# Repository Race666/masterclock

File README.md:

# Mutteruhrsteuerung

Firmware und Schaltungen zum Steuern von sog. Nebenuhren (z.B. Bahnhofsuhren)

Dokumentation und Details auf [albert-hetzles.de](http://albert-hetzles.de/mutteruhr/index.shtml)

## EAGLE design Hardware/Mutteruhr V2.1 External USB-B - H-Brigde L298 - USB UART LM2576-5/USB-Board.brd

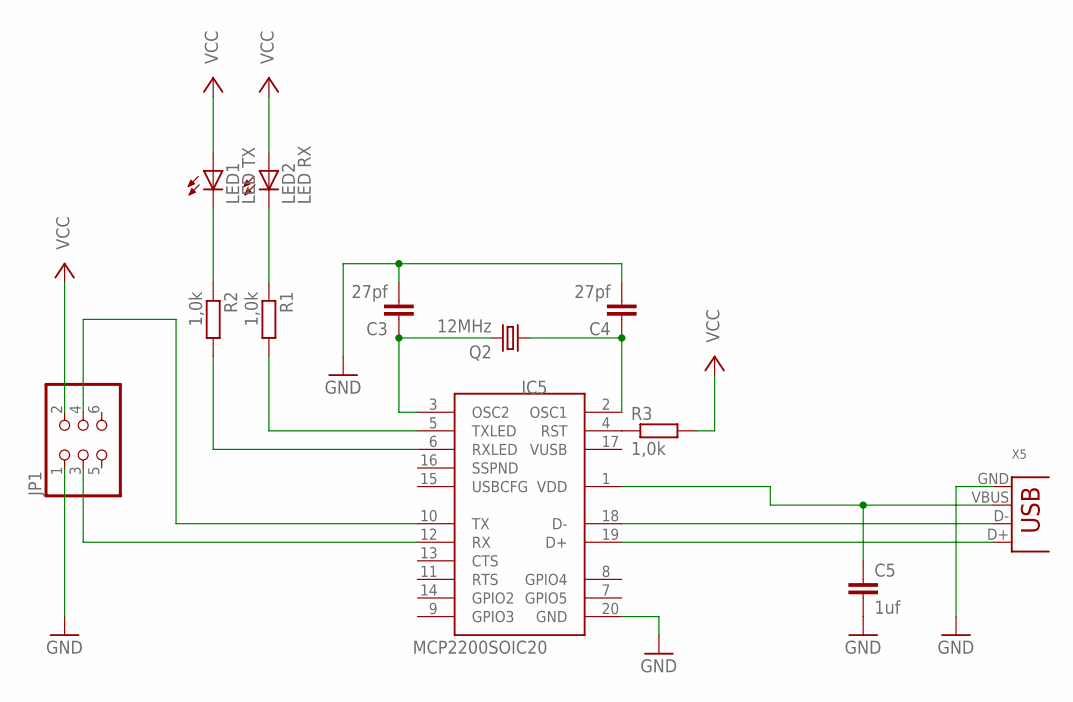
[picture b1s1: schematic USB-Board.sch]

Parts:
C3, C4: 27pf; C050-024X044
C5: 1uf; C5B5.5
IC5: MCP2200SOIC20; SOIC20
JP1: PINHD-2X3; 2X03
LED1: LED TX; LED3MM
LED2: LED RX; LED3MM
Q2: 12MHz; HC18U-V
R1, R2, R3: 1,0k; 0207/10
X5: USB-B-H

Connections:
GND: C3.2, C4.2, C5.2, IC5.20 (GND), JP1.1, X5.GND
unnamed: LED1.K (C), R2.1
unnamed: LED2.K (C), R1.1
unnamed: IC5.18 (D-), X5.D-
unnamed: IC5.19 (D+), X5.D+
unnamed: IC5.10 (TX), JP1.4
unnamed: IC5.12 (RX), JP1.3
unnamed: IC5.4 (RST), R3.1
unnamed: C3.1, IC5.3 (OSC2), Q2.2
unnamed: C4.1, IC5.2 (OSC1), Q2.1
unnamed: IC5.6 (RXLED), R2.2
unnamed: IC5.5 (TXLED), R1.2
unnamed: C5.1, IC5.1 (VDD), X5.VBUS
VCC: JP1.2, LED1.A, LED2.A, R3.2

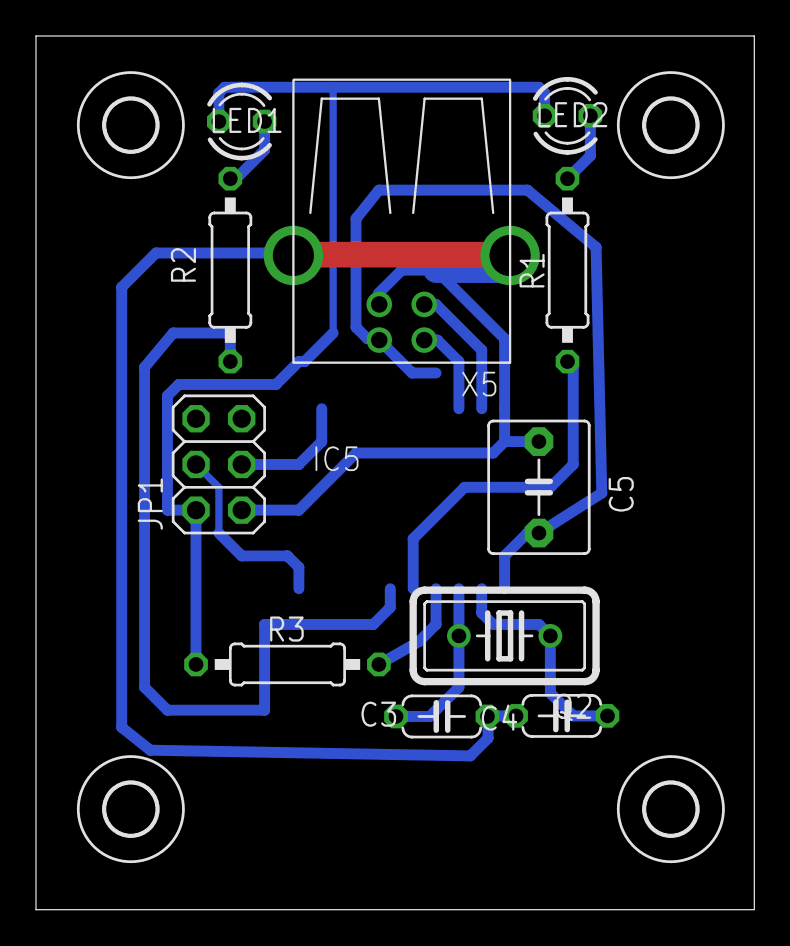
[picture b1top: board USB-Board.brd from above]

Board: 2 copper layers, 39.9 x 48.5 mm, 16 parts (1 on the bottom side), 14 nets.

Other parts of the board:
U$1, U$2, U$3, U$4: 2,8

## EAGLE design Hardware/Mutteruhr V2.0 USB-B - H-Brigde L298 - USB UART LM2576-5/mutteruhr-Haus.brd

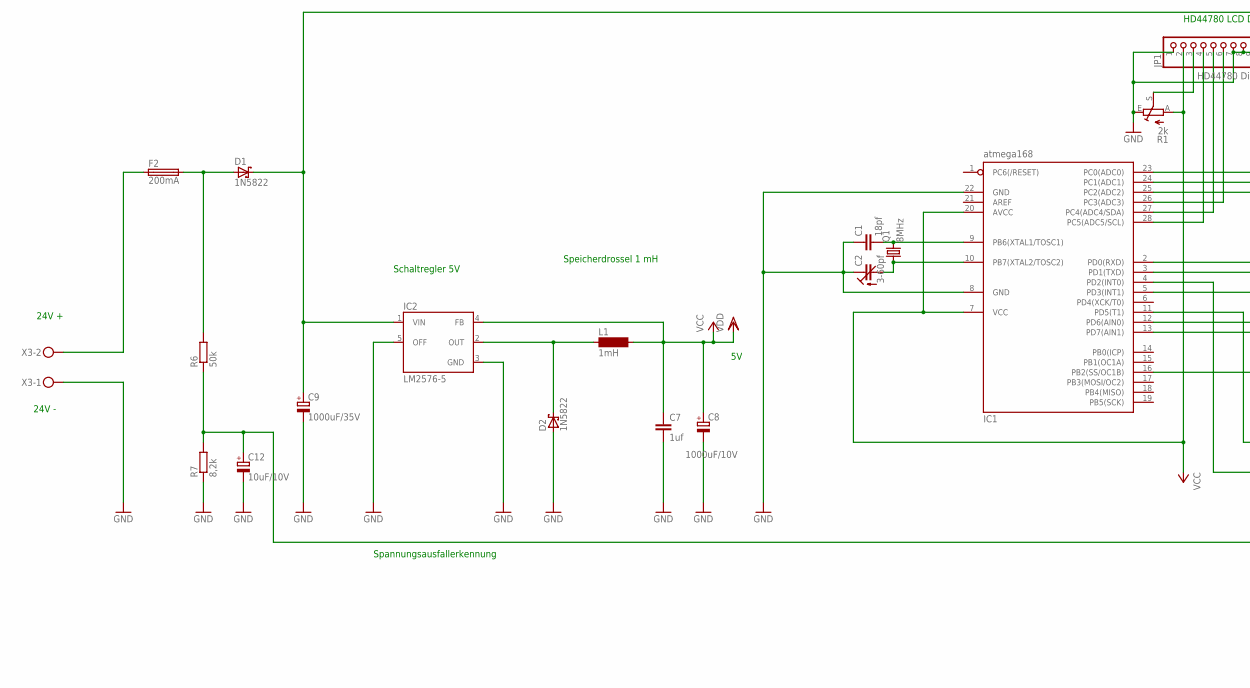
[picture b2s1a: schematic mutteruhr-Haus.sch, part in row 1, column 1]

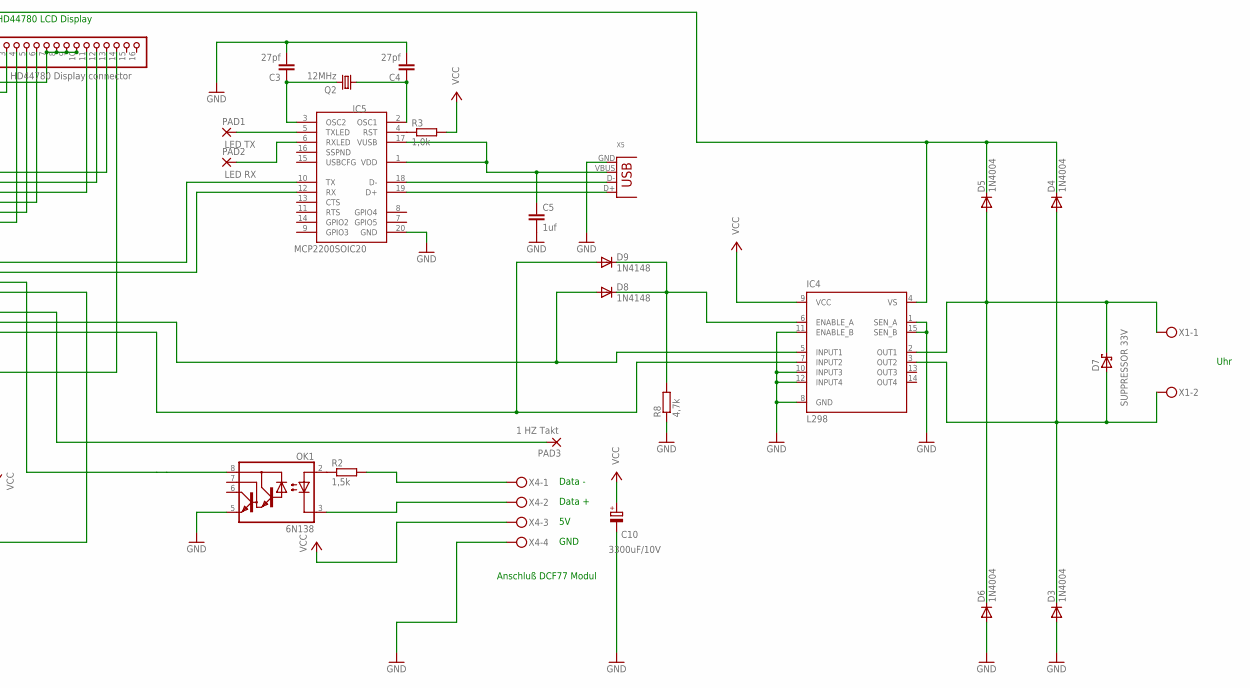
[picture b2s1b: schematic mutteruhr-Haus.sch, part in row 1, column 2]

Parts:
C1: 18pf; C050-024X044
C2: 3-60pf; CTRIM3050.505
C3, C4: 27pf; C050-024X044
C5, C7: 1uf; C5B5.5
C8: 1000uF/10V; E5-8,5
C9: 1000uF/35V; E5-8,5
C10: 3300uF/10V; E7,5-16
C12: 10uF/10V; E5-5
D1, D2: 1N5822; DO41-7.6
D3, D4, D5, D6: 1N4004; DO41-10
D7: SUPPRESSOR 33V; DO41-10
D8, D9: 1N4148; DO35-7
F2: 200mA; SH25
IC1: atmega168; DIL28-3
IC2: LM2576-5; TO220-5
IC4: L298; MULTIWATT-15
IC5: MCP2200SOIC20; SOIC20
JP1: HD44780 Display connector; 1X16
L1: 1mH; BS11
OK1: 6N138; DIL08
PAD1: LED TX; 2,54/0,8
PAD2: LED RX; 2,54/0,8
PAD3: 1 HZ Takt; 2,54/0,8
Q1: 8MHz; HC18U-V
Q2: 12MHz; HC18U-V
R1: 2k; RS3
R2: 1,5k; 0207/10
R3: 1,0k; 0207/10
R6: 50k; 0207/10
R7: 8,2k; 0207/10
R8: 4,7k; 0207/10
X1, X3: MKDSN1,5/2-5,08
X4: MKDSN1,5/4-5,08
X5: USB-B-H

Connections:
GND: C1.1, C2.1 (E), C3.2, C4.2, C5.2, C7.2, C8.-, C9.-, C10.-, C12.-, D2.A, D3.A, D6.A, IC1.8 (GND), IC1.22 (GND), IC2.3 (GND), IC2.5 (OFF), IC4.1 (SEN_A), IC4.8 (GND), IC4.10 (INPUT3), IC4.11 (ENABLE_B), IC4.12 (INPUT4), IC4.15 (SEN_B), IC5.20 (GND), JP1.1, JP1.7, JP1.8, JP1.9, JP1.10, OK1.5 (GND), R1.E, R7.1, R8.1, X3.1, X4.4, X5.GND
unnamed: IC1.4 (PD2(INT0)), OK1.8 (VCC)
unnamed: C1.2, IC1.9 (PB6(XTAL1/TOSC1)), Q1.2
unnamed: C2.2 (A), IC1.10 (PB7(XTAL2/TOSC2)), Q1.1
unnamed: IC1.23 (PC0(ADC0)), JP1.13
unnamed: IC1.24 (PC1(ADC1)), JP1.12
unnamed: IC1.25 (PC2(ADC2)), JP1.11
unnamed: IC1.26 (PC3(ADC3)), JP1.6
unnamed: IC1.27 (PC4(ADC4/SDA)), JP1.5
unnamed: IC1.28 (PC5(ADC5/SCL)), JP1.4
unnamed: IC1.16 (PB2(SS/OC1B)), JP1.14
unnamed: IC5.18 (D-), X5.D-
unnamed: JP1.3, R1.S
unnamed: IC5.19 (D+), X5.D+
unnamed: IC1.2 (PD0(RXD)), IC5.10 (TX)
unnamed: IC1.3 (PD1(TXD)), IC5.12 (RX)
unnamed: IC5.4 (RST), R3.1
unnamed: C3.1, IC5.3 (OSC2), Q2.2
unnamed: C4.1, IC5.2 (OSC1), Q2.1
unnamed: IC5.6 (RXLED), PAD2.1
unnamed: IC5.5 (TXLED), PAD1.1
unnamed: D9.A, IC1.13 (PD7(AIN1)), IC4.7 (INPUT2)
unnamed: OK1.2 (A), R2.1
unnamed: C5.1, IC5.1 (VDD), IC5.17 (VUSB), X5.VBUS
unnamed: IC1.11 (PD5(T1)), PAD3.1
unnamed: D1.A, F2.2, R6.2
unnamed: OK1.3 (C), X4.2
unnamed: C9.+, D1.C, D4.C, D5.C, IC2.1 (VIN), IC4.4 (VS)
unnamed: F2.1, X3.2
unnamed: R2.2, X4.1
unnamed: C12.+, IC1.5 (PD3(INT1)), R6.1, R7.2
unnamed: D2.C, IC2.2 (OUT), L1.1
unnamed: D8.C, D9.C, IC4.6 (ENABLE_A), R8.2
unnamed: D3.C, D4.A, D7.A, IC4.3 (OUT2), X1.2
unnamed: D8.A, IC1.12 (PD6(AIN0)), IC4.5 (INPUT1)
unnamed: D5.A, D6.C, D7.C, IC4.2 (OUT1), X1.1
VCC: C7.1, C8.+, C10.+, IC1.7 (VCC), IC1.20 (AVCC), IC2.4 (FB), IC4.9 (VCC), JP1.2, L1.2, R1.A, R3.2, X4.3

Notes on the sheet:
Speicherdrossel 1 mH
Schaltregler 5V
HD44780 LCD Display
24V +
24V -
Anschluß DCF77 Modul
GND
Data +
Data -
Uhr
Spannungsausfallerkennung

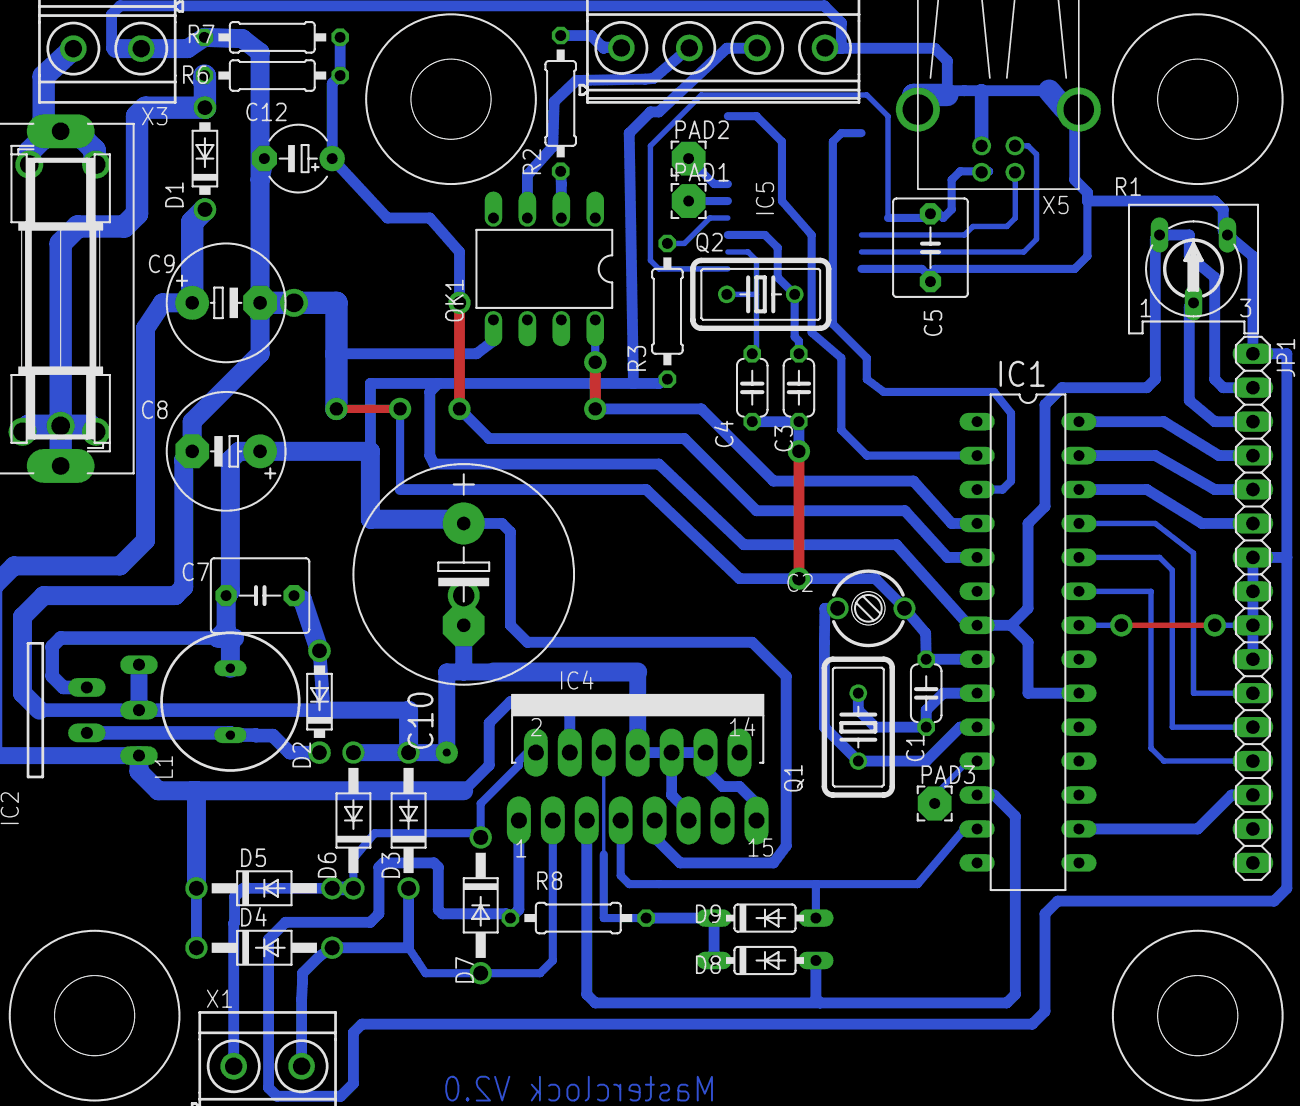
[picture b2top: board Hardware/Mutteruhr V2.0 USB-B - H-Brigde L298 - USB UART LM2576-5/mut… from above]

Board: 2 copper layers, 46 parts (1 on the bottom side), 37 nets.

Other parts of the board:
U$1, U$2, U$3, U$4: DRIL-6

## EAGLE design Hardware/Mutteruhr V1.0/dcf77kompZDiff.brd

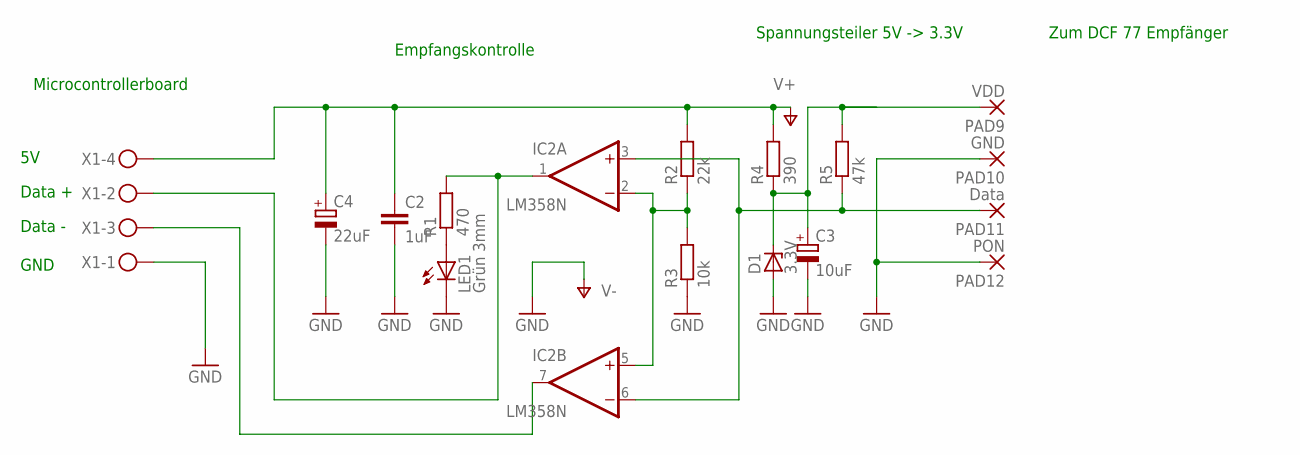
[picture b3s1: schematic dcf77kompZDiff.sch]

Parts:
C2: 1uF; C050-050X075
C3: 10uF; E2,5-5
C4: 22uF; E5-10,5
D1: 3.3V; DO34Z7
IC2: LM358N; DIL08
LED1: Grün 3mm; LED5MM
PAD9: VDD; 1,6/0,9
PAD10: GND; 1,6/0,9
PAD11: Data; 1,6/0,9
PAD12: PON; 1,6/0,9
R1: 470; 0207/10
R2: 22k; 0207/10
R3: 10k; 0207/10
R4: 390; 0207/10
R5: 47k; 0207/10
X1: MKDSN1,5/4-5,08

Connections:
GND: C2.2, C3.-, C4.-, D1.A, IC2.4 (V-), LED1.K (C), PAD10.1, PAD12.1, R3.1, X1.1
unnamed: C3.+, D1.C, PAD9.1, R4.1, R5.2
unnamed: LED1.A, R1.1
unnamed: IC2.1 (OUT), R1.2, X1.2
unnamed: IC2.7 (OUT), X1.3
unnamed: IC2.2 (-IN), IC2.5 (+IN), R2.1, R3.2
unnamed: IC2.3 (+IN), IC2.6 (-IN), PAD11.1, R5.1
V+: C2.1, C4.+, IC2.8 (V+), R2.2, R4.2, X1.4

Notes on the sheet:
Zum DCF 77 Empfänger
Microcontrollerboard
Empfangskontrolle
Spannungsteiler 5V -> 3.3V
Data +
Data -
GND

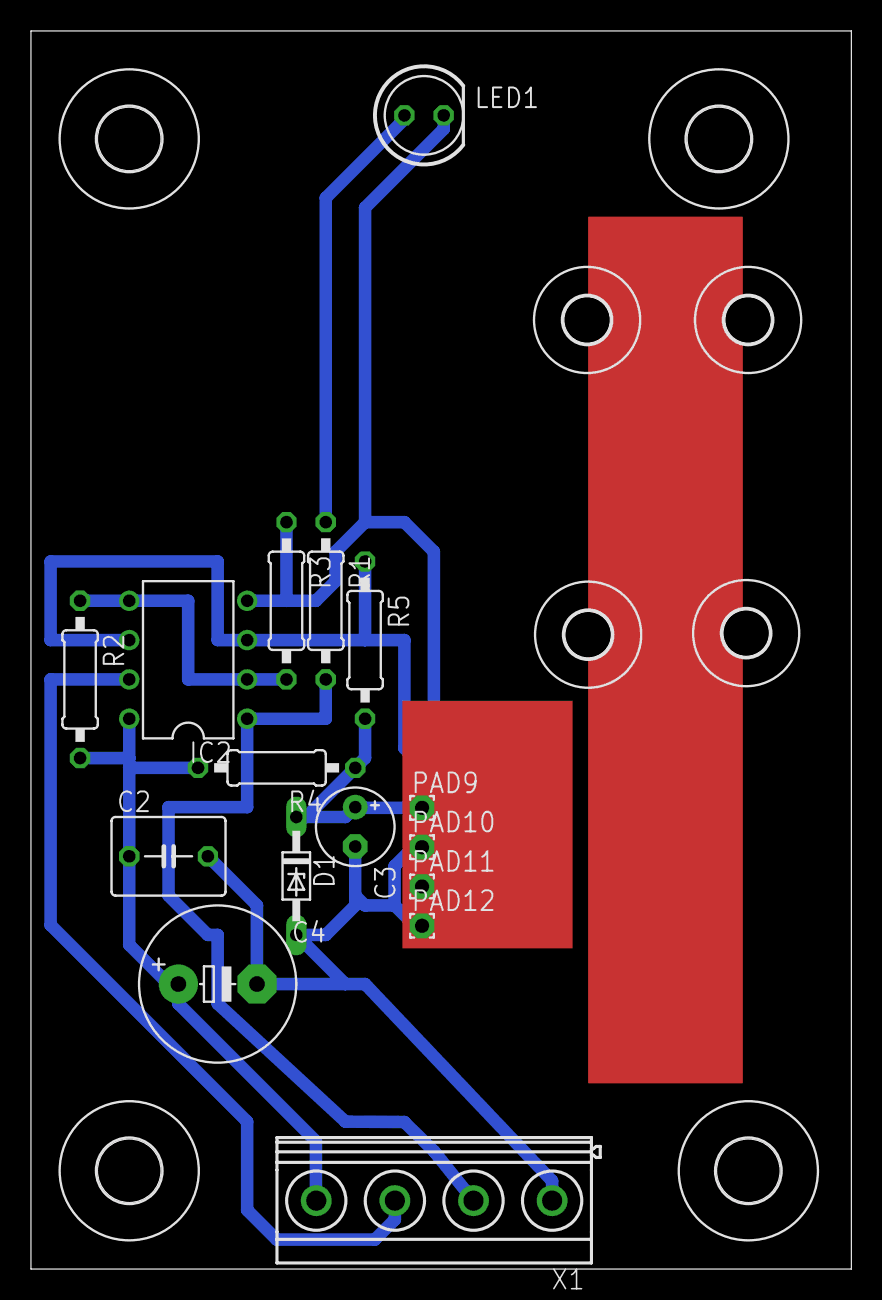
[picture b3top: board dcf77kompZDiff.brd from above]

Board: 2 copper layers, 53.0 x 80.0 mm, 24 parts (0 on the bottom side), 8 nets.

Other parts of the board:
U$1, U$2, U$3, U$4: 4,1
U$5, U$6, U$7, U$8: 3,0

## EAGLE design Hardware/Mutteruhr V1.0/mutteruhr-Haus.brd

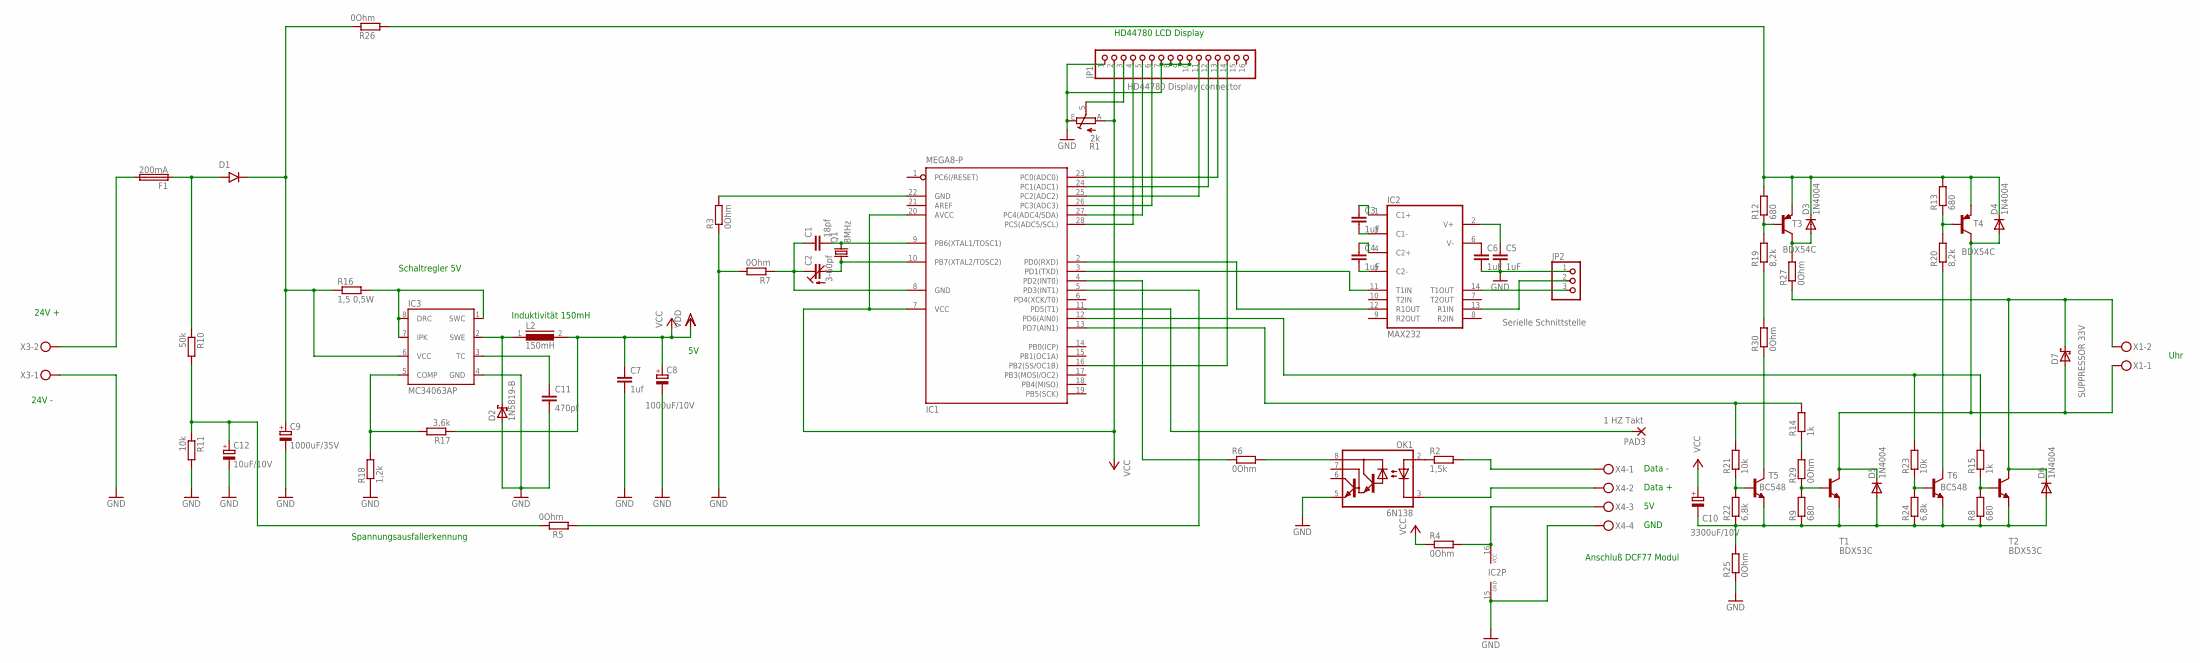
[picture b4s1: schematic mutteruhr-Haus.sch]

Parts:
C1: 18pf; C050-024X044
C2: 3-60pf; CTRIM3050.505
C3, C4, C5, C6: 1uF; C5B5.5
C7: 1uf; C5B5.5
C8: 1000uF/10V; E5-8,5
C9: 1000uF/35V; E5-8,5
C10: 3300uF/10V; E7,5-16
C11: 470pf; C5B5.5
C12: 10uF/10V; E5-5
D1: 1N4001; DO41-10
D2: 1N5819-B; DO41-7.6
D3, D4, D5, D6: 1N4004; DO41-10
D7: SUPPRESSOR 33V; DO41-10
F1: 200mA; GSH15
IC1: MEGA8-P; DIL28-3
IC2: MAX232; DIL16
IC3: MC34063AP; DIL-08
JP1: HD44780 Display connector; 1X16
JP2: Serielle Schnittstelle; 1X03
L2: 150mH; 82114R
OK1: 6N138; DIL08
PAD3: 1 HZ Takt; 2,54/0,8
Q1: 8MHz; HC18U-V
R1: 2k; RS3
R2: 1,5k; 0204/7
R3, R4, R5, R6, R7, R25, R26: 0Ohm; 0204/7
R8, R9, R12, R13: 680; 0207/10
R10: 50k; 0204/7
R11: 10k; 0204/7
R14, R15: 1k; 0207/10
R16: 1,5 0,5W; 0204/7
R17: 3,6k; 0204/7
R18: 1,2k; 0204/7
R19, R20: 8,2k; 0207/10
R21, R23: 10k; 0207/10
R22, R24: 6,8k; 0204V
R27, R29, R30: 0Ohm; 0207/10
T1, T2: BDX53C; TO220V
T3, T4: BDX54C; TO220V
T5, T6: BC548; TO92-EBC
X1, X3: MKDSN1,5/2-5,08
X4: MKDSN1,5/4-5,08

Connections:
GND: C5.2, C6.2, C7.2, C8.-, C9.-, C11.2, C12.-, D2.A, IC2.15 (GND), IC3.4 (GND), JP1.1, JP1.7, JP1.8, JP1.9, JP1.10, JP2.1, OK1.5 (GND), R1.E, R3.1, R7.2, R11.2, R18.1, R25.1, X3.1, X4.4
unnamed: IC1.4 (PD2(INT0)), R6.1
unnamed: C1.2, IC1.9 (PB6(XTAL1/TOSC1)), Q1.2
unnamed: C2.2 (A), IC1.10 (PB7(XTAL2/TOSC2)), Q1.1
unnamed: IC1.23 (PC0(ADC0)), JP1.13
unnamed: IC1.24 (PC1(ADC1)), JP1.12
unnamed: IC1.25 (PC2(ADC2)), JP1.11
unnamed: IC1.26 (PC3(ADC3)), JP1.6
unnamed: IC1.27 (PC4(ADC4/SDA)), JP1.5
unnamed: IC1.28 (PC5(ADC5/SCL)), JP1.4
unnamed: IC1.16 (PB2(SS/OC1B)), JP1.14
unnamed: IC2.13 (R1IN), JP2.2
unnamed: JP1.3, R1.S
unnamed: IC1.3 (PD1(TXD)), IC2.11 (T1IN)
unnamed: IC1.2 (PD0(RXD)), IC2.12 (R1OUT)
unnamed: C6.1, IC2.6 (V-)
unnamed: C5.1, IC2.2 (V+)
unnamed: C3.2, IC2.3 (C1-)
unnamed: C3.1, IC2.1 (C1+)
unnamed: C4.1, IC2.4 (C2+)
unnamed: C4.2, IC2.5 (C2-)
unnamed: IC2.14 (T1OUT), JP2.3
unnamed: IC1.13 (PD7(AIN1)), R14.2, R21.2
unnamed: IC1.5 (PD3(INT1)), R5.1
unnamed: D3.C, D4.C, R12.2, R13.2, R26.1, T3.3 (E), T4.3 (E)
unnamed: IC1.11 (PD5(T1)), PAD3.1
unnamed: D1.A (ANODE), F1.1, R10.1
unnamed: OK1.3 (C), X4.2
unnamed: C9.+, D1.C (CATHODE), IC3.6 (VCC), R16.1, R26.2
unnamed: F1.2, X3.2
unnamed: OK1.2 (A), R2.1
unnamed: IC1.22 (GND), R3.2
unnamed: R2.2, X4.1
unnamed: C12.+, R5.2, R10.2, R11.1
unnamed: OK1.8 (VCC), R6.2
unnamed: C1.1, C2.1 (E), IC1.8 (GND), R7.1
unnamed: IC2.16 (VCC), R4.2, X4.3
unnamed: IC3.5 (COMP), R17.2, R18.2
unnamed: C11.1, IC3.3 (TC)
unnamed: D2.C, IC3.2 (SWE), L2.1
unnamed: IC3.1 (SWC), IC3.7 (IPK), IC3.8 (DRC), R16.2
unnamed: C10.-, D5.A, D6.A, R8.1, R9.1, R22.1, R24.1, R25.2, T1.3 (E), T2.3 (E), T5.E, T6.E
unnamed: R21.1, R22.2, T5.B
unnamed: R9.2, R29.1, T1.1 (B)
unnamed: IC1.12 (PD6(AIN0)), R15.2, R23.2
unnamed: R23.1, R24.2, T6.B
unnamed: R8.2, R15.1, T2.1 (B)
unnamed: D4.A, D5.C, D7.A, T1.2 (C), T4.2 (C), X1.1
unnamed: D3.A, R27.2, T3.2 (C)
unnamed: R13.1, R20.2, T4.1 (B)
unnamed: R12.1, R19.2, T3.1 (B)
unnamed: R30.1, T5.C
unnamed: D6.C, D7.C, R27.1, T2.2 (C), X1.2
unnamed: R14.1, R29.2
unnamed: R20.1, T6.C
unnamed: R19.1, R30.2
VCC: C7.1, C8.+, C10.+, IC1.7 (VCC), IC1.20 (AVCC), JP1.2, L2.2, R1.A, R4.1, R17.1

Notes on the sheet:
Induktivität 150mH
Schaltregler 5V
HD44780 LCD Display
24V +
24V -
Anschluß DCF77 Modul
GND
Data +
Data -
Uhr
Spannungsausfallerkennung

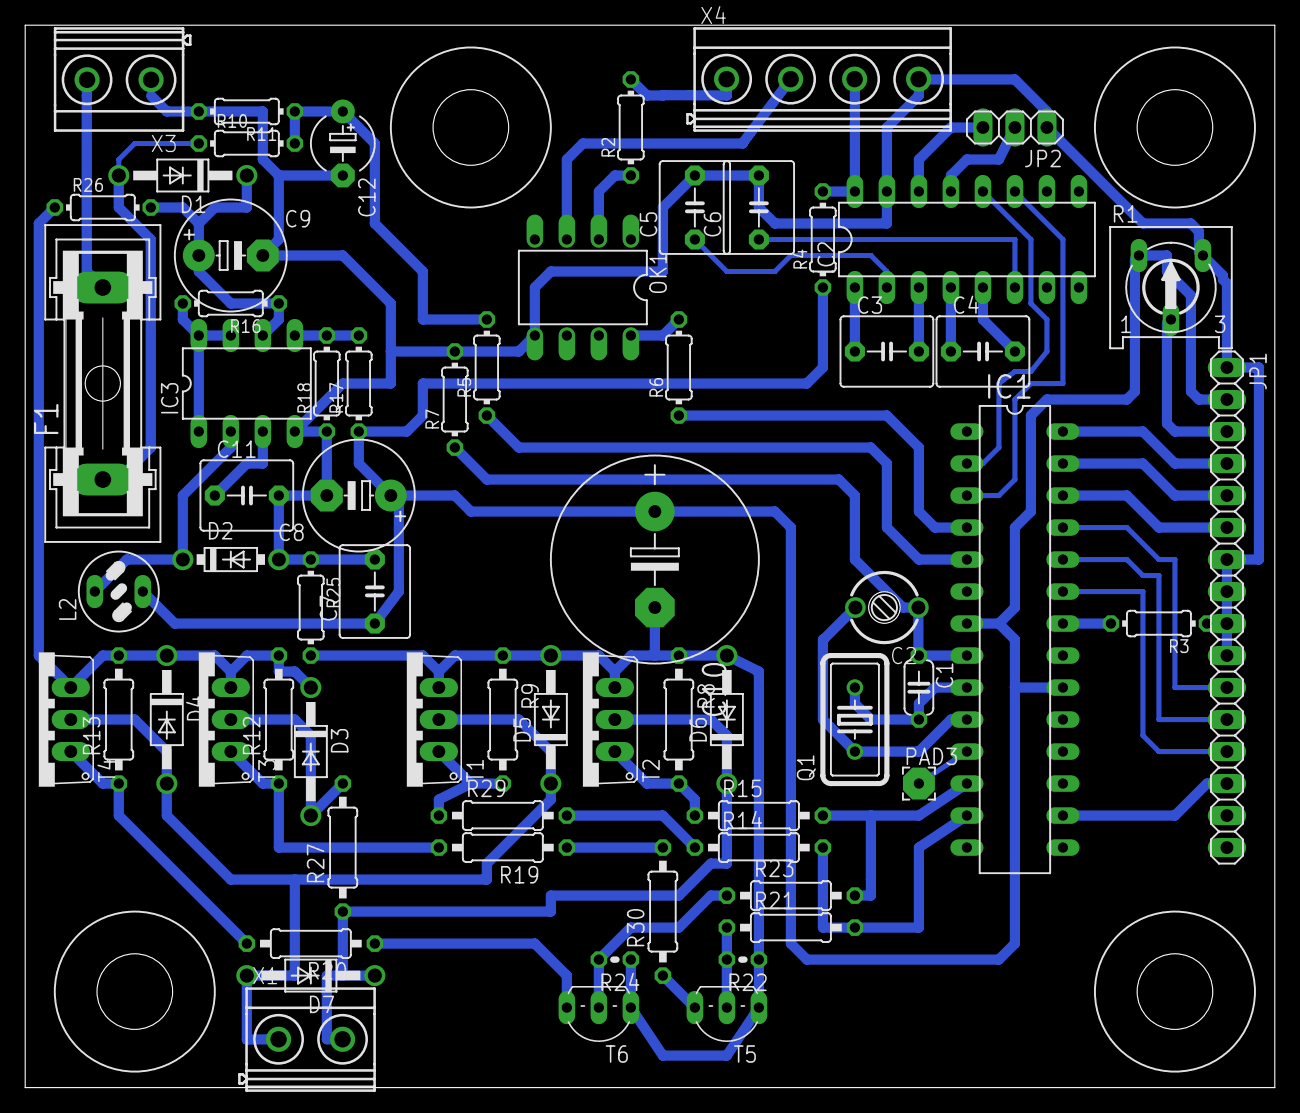
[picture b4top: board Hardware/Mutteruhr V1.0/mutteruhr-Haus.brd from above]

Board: 1 copper layer, 99.2 x 84.3 mm, 71 parts (0 on the bottom side), 57 nets.

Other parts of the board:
U$1, U$2, U$3, U$4: DRIL-6

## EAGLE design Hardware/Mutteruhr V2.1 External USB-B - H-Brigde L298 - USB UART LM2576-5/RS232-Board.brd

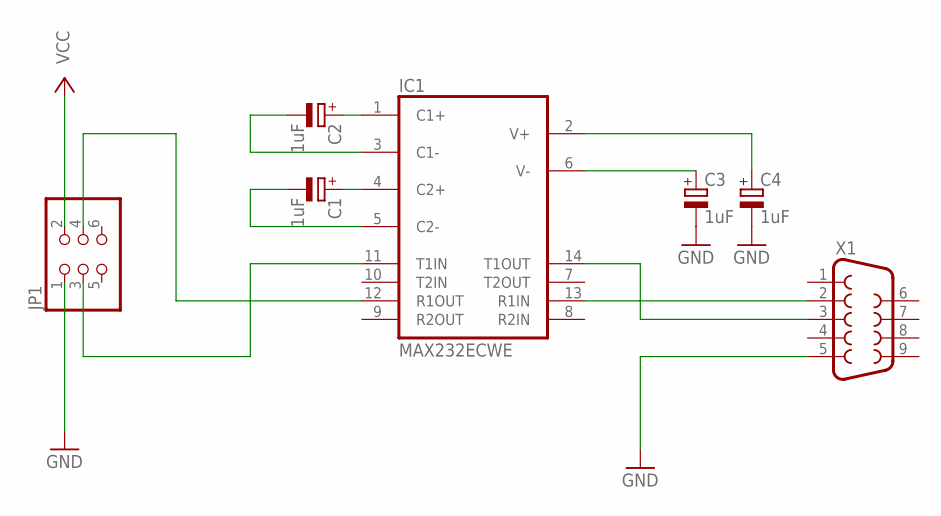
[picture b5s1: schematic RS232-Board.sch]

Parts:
C1, C2, C3, C4: 1uF; E2,5-6E
IC1: MAX232ECWE; SO16L
JP1: PINHD-2X3; 2X03
X1: F09H

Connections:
GND: C3.-, C4.-, IC1.15 (GND), JP1.1, X1.5
unnamed: C1.+, IC1.4 (C2+)
unnamed: C1.-, IC1.5 (C2-)
unnamed: IC1.13 (R1IN), X1.2
unnamed: C2.-, IC1.3 (C1-)
unnamed: C2.+, IC1.1 (C1+)
unnamed: C3.+, IC1.6 (V-)
unnamed: C4.+, IC1.2 (V+)
unnamed: IC1.14 (T1OUT), X1.3
unnamed: IC1.12 (R1OUT), JP1.4
unnamed: IC1.11 (T1IN), JP1.3
VCC: IC1.16 (VCC), JP1.2

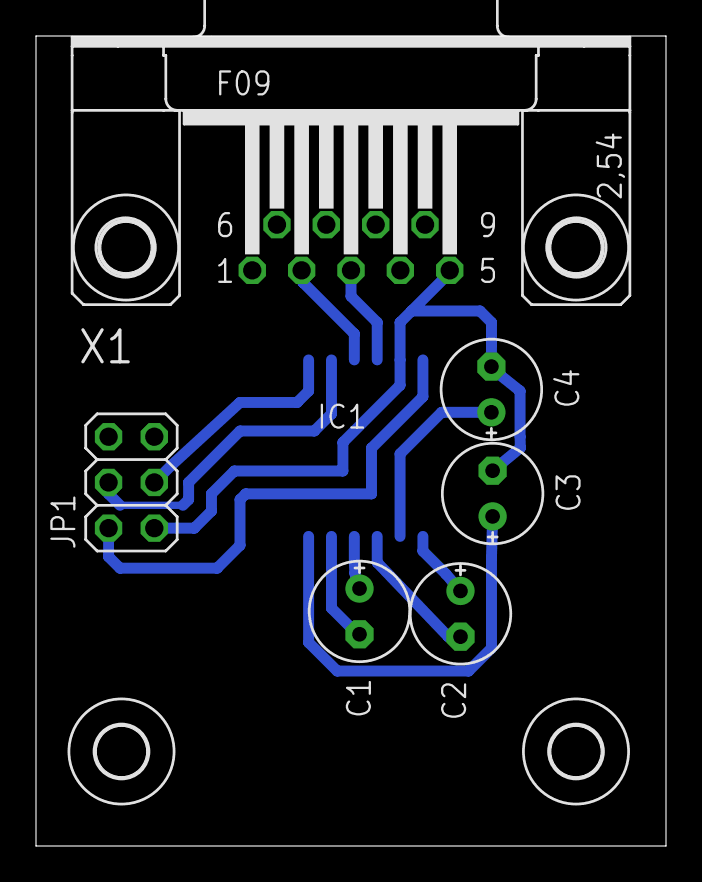
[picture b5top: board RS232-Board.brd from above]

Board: 2 copper layers, 35.0 x 45.0 mm, 11 parts (1 on the bottom side), 12 nets.

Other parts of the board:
U$1, U$2, U$3, U$4: 2,8

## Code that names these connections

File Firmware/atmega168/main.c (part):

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V1.05	  06.12.2010 michael@albert-hetzles.de Bug im  Protokoll gd7 behoben		
V1.06b2   25.10.2011 michael@albert-hetzles.de Trotz bDCF77=false wurde syncronisiert		
          20.12.2012 michael@albert-hetzles.de Peridodenzeit der Impulse beim synchronieren änderbar, default 1sec	
V1.06b4	  24.02.2013 michael@albert-hetzles.de Bug!!! Inkonsitenz Schaltplan und Programm OUTPUT_PULSE_EVEN PB0 -> PD6	   
V1.07	  06.03.2013 michael@albert-hetzles.de 1.07=1.06b4	
V1.08b1   01.03.2014 michael@albert-hetzles.de Bug in fInitLEDIOPorts Zeile 1573 	PORTD -> PORTC geändert
V1.08     22.06.2014 michael@albert-hetzles.de V1.08b1 -> V1.08
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// Max Pulsweite
#define MAX_PULSE_WIDTH_IN100MS 8
// Ausgang ungerade Minute
#define OUTPUT_PULSE_ODD PD7
// Ausgang gerade Minute
#define OUTPUT_PULSE_EVEN PD6
// Ausgang gerade Minute an
#define SET_PULSE_ODD {PORTD|=(1<<OUTPUT_PULSE_ODD);}
// Ausgang ungerade Minute an
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#define RESET_PULSE_EVEN {PORTD&=~(1<<OUTPUT_PULSE_EVEN);}

// Eingang für die Netzspannungsausfallerkennung
#define POWER_SUPPLY_ACTIVE_PIN PD3
// Macro zur Abfrage Netzspannungsausfallerkennung
#define POWER_SUPPLY_ACTIVE ((PIND) & (1<<POWER_SUPPLY_ACTIVE_PIN))
// Eingang für die LCD Display Abschaltung
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

// 1HZ Blink Ausgang
#define PIN_1HZ_BLINK PD5

// Ausgänge für LED's definieren
// Ausgang wenn DCF77 Daten empfangen werden
// Blinken=warte auf Daten, leuchten=Empfange Daten, aus=DCF77 Off
// Uhr syncronisiert
#define PIN_CLOCK_IS_SYNCING PC5
// DCF77 Health Status Leuchtet=DCF77 letzter DCF77 Empfang <1h; blinkt=DCF77 letzter DCF77 Empfang <24h;aus DCF77 letzter DCF77 Empfang >24h 
#define PIN_LED_DCF77_HEALTH_STATE PC4
// Gültiges DCF77 Paket empfangen
#define PIN_LED_DCF77_RETURN_STATE_OK PC3
// Ungültiges DCF77 Paket empfangen
#define PIN_LED_DCF77_RETURN_STATE_ERROR PC2
// Empfangsstatus blink=warte auf Daten, leuchtet=Empfange Daten
#define PIN_LED_DCF77_CURRENT_STATUS PC1



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#define DCF_PULSE_AND_PAUSE_CYCLE_SUM_MAX 8212
// Zeit für die die DCF Daten gültig sind
#define DCF77_IS_VALID_FOR_SECONDS 59
// EIngangspin für das DCF77 Signal, ISR0, PD2
#define DCF77_INPUT_PIN PD2
// Pegel für DCF In
#define HIGH 1
#define LOW 0
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	// EICRA |= (1<<ISC11);
	// ISR1 Steigende/Fallende Flanke
	EICRA |= (1<<ISC10);
	// Interrupt 1 (PD3)
	EIMSK |= (1<<INT1);
}
static void fInitLEDIOPorts(void){
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	// EICRA |= (1<<ISC01);
	//Steigende Flanke
	// EICRA |= (1<<ISC01) | (1<<ISC00);
	// Interrupt 0 (PD2)
	EIMSK |= (1<<INT0);
	// oder GICR |= (1<<INT0);
	tDCF77DateTime.iDCF77Status=DCF77_WAIT_FOR_SYNCING;
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
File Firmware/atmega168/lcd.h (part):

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#define LCD_DATA1_PORT   PORTC     /**< port for 4bit data bit 1 */
#define LCD_DATA2_PORT   PORTC     /**< port for 4bit data bit 2 */
#define LCD_DATA3_PORT   PORTB     /**< port for 4bit data bit 3 */
#define LCD_DATA0_PIN    PC2            /**< pin for 4bit data bit 0  */
#define LCD_DATA1_PIN    PC1            /**< pin for 4bit data bit 1  */
#define LCD_DATA2_PIN    PC0            /**< pin for 4bit data bit 2  */
#define LCD_DATA3_PIN    PB2            /**< pin for 4bit data bit 3  */
#define LCD_RS_PORT      PORTC     /**< port for RS line         */
#define LCD_RS_PIN       PC5            /**< pin  for RS line         */
#define LCD_RW_PORT      PORTC     /**< port for RW line         */
#define LCD_RW_PIN       PC4            /**< pin  for RW line         */
#define LCD_E_PORT       PORTC     /**< port for Enable line     */
#define LCD_E_PIN        PC3            /**< pin  for Enable line     */

#elif defined(__AVR_AT90S4414__) || defined(__AVR_AT90S8515__) || defined(__AVR_ATmega64__) || \
      defined(__AVR_ATmega8515__)|| defined(__AVR_ATmega103__) || defined(__AVR_ATmega128__) || \
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
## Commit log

2010-03-06 v1.07
2010-07-09 v1.00
2010-08-09 v1.01
2010-08-27 v1.02
2010-08-31 v1.03
2010-11-23 v1.04
2010-12-06 v1.05
2013-02-24 v1.06b4
2014-06-22 v1.08
2014-09-16 v1.09
2016-11-09 Hardware V1.0, V2.0, V2.1 hinzugefuegt
2018-10-23 Branch linux-build. Umstellung WinAVR -> Linux (Debian)
2019-09-18 Diverse bool variablen nach stdbool migiert. DCF77 Debug variablen hinzugefuegt
2019-09-18 dbgdcf command nach _dbgdcf umgestellt
2019-09-18 iMenuPosition -> iShellPosition
2019-09-18 Umstellung Shell Position auf Konstanten. 0 -> SHELL_MENU_PROMPT
2019-09-18 Umstellung Shell Position auf Konstanten. 1 -> SHELL_MENU_SMT
2019-09-18 Umstellung Shell Position auf Konstanten. 2 -> SHELL_MENU_NST
2019-09-18 Umstellung Shell Position auf Konstanten. 3 -> SHELL_MENU_AST
2019-09-18 Umstellung Shell Position auf Konstanten. 4 -> SHELL_MENU_DCF_ON_OFF
2019-09-18 Umstellung Shell Position auf Konstanten. 5 -> SHELL_MENU_PST
2019-09-18 Umstellung Shell Position auf Konstanten. 6 -> SHELL_MENU_SSM
2019-09-18 Umstellung Shell Position auf Konstanten. 7 -> SHELL_MENU_SPW
2019-09-18 Umstellung auf Konstanten fuer iDisplayPage. 0->DISPLAY_PAGE_TIME_ON_SLAVES,1->DISPLAY_PAGE_CLOCK_IS_SYNCING
2019-09-18 Umstellung auf Konstanten fuer iDisplayPage. 2->DISPLAY_PAGE_DCF_OP_MODE, 3->DISPLAY_PAGE_DCF_STATUS, 4->DISPLAY_PAGE_DCF_LAST_RESULT, 5->DISPLAY_PAGE_DCF_RECEIVE_BIT_STATE
2019-09-18 Umstellung auf Konstanten fuer iDisplayPage. 6->DISPLAY_PAGE_DCF_SHOW_DATE_TIME, 7->DISPLAY_PAGE_CLOCK_SYNC_MODE_12H_24H, 8->DISPLAY_PAGE_INVALID
2019-09-18 Display update geaendert von 1sec auf 0.5sec. Displaypage fuer DCF Debug aktiviert
2019-09-18 Ueberpruefung ob Display Page gueltig ist von main nach fExecuteEverySecond umgezogen
2019-09-18 Neue Funktion fGetLeftAlignedFilledUpString, Preproc DCF_DEBUG vervollstaendigt
2019-09-19 Neue Funktion fGetLeftRightAlignedFilledUpString, 2. sTemp Variable -> sTemp1 und sTemp2. Ausgabe von DISPLAY_PAGE_DCF_DEBUG_TIMING ergaenzt
2019-09-20 Ausgabe ueber Display eingebaut
2020-07-01 Fehler an USB MCP2200 VDD gefixt. Verbindung Pin 1 - 17 getrennt
2020-07-01 Fehler an USB MCP2200 VDD gefixt. Verbindung Pin 1 - 17 getrennt: Branch linux-build
2020-09-30 Sekunden Counter mit DCF synchronsieren
2020-09-30 Precompiled maix.hex main.epp
2023-12-17 Hardware Revision V3
